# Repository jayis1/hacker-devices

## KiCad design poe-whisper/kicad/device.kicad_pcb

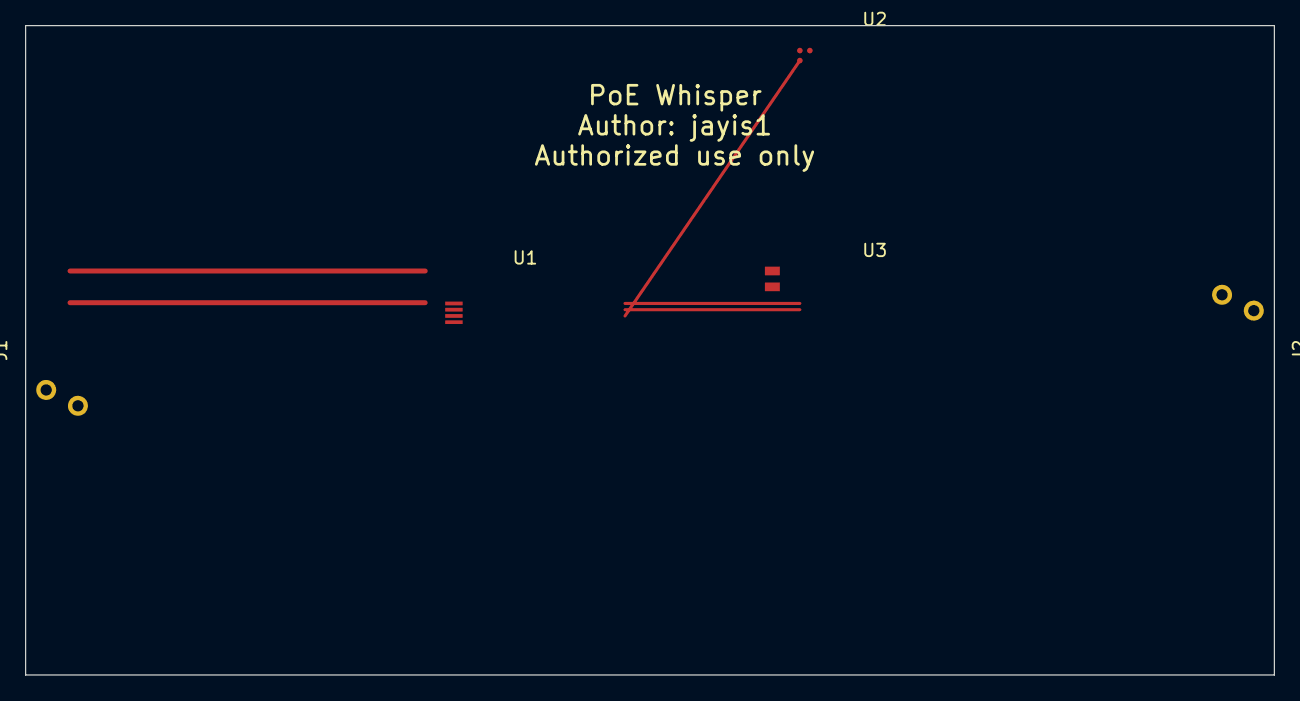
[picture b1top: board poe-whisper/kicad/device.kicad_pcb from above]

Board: 2 copper layers, 100.0 x 52.0 mm, 5 parts (0 on the bottom side), 4 nets.

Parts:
J1: RJ45_PSE_IN; RJ45_Amphenol_RJHSE538X
J2: RJ45_PD_OUT; RJ45_Amphenol_RJHSE538X
U1: STM32H563RIT6; LQFP-64_10x10mm_P0.5mm
U2: MachXO3LF-2100C; caBGA-256_14x14mm_Layout16x16_P0.8mm
U3: ESP32-C3-MINI-1

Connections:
+3V3: U1.4, U3.1
BROWNOUT_GATE: U1.3, U2.B1
POE_RETURN: J1.2, J2.2
POE_VIN: J1.1, J2.1

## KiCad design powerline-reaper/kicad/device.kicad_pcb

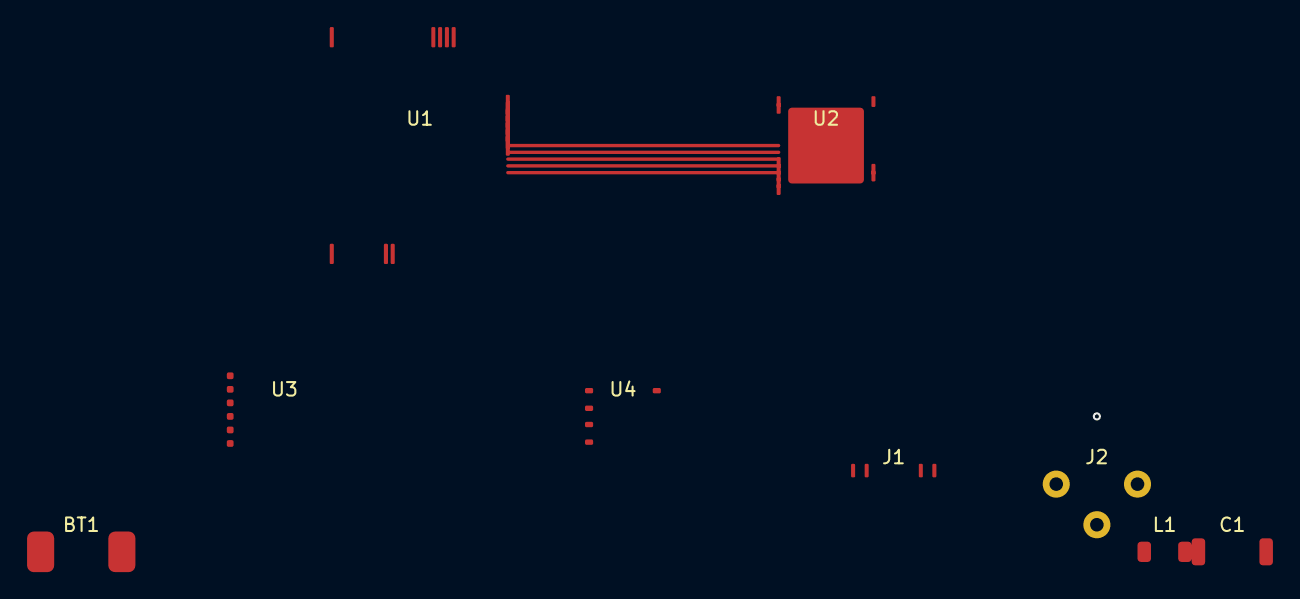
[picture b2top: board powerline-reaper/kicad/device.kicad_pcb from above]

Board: 4 copper layers, 9 parts (0 on the bottom side), 16 nets.

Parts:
BT1: LiPo_1000mAh; BatteryHolder_Keystone_1042
C1: X2Y_100nF_275V; C_2220_5764Metric
J1: USB_C; USB_C_Receptacle
J2: AC_Mains; IEC_C14
L1: CMC_100uH; L_0805_2012Metric
U1: STM32H743VIT6; LQFP-100_14x14mm_P0.5mm
U2: QCA7420; QFN-48-1EP_7x7mm_P0.5mm_EP5.6x5.6mm
U3: nRF52840; nRF52840-module
U4: ADuM1402; SOIC-8_3.9x4.9mm_P1.27mm

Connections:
+3V3: U1.21, U2.1, U3.1
BLE_CTS: U1.81, U3.6
BLE_RTS: U1.80, U3.5
BLE_RX: U1.79, U3.4
BLE_TX: U1.78, U3.3
GND: BT1.-, J1.A1, J2.E, U1.1, U2.2, U2.49, U3.2
LINE_AC: C1.1, J2.L, L1.1, U2.30
NEUTRAL_AC: C1.2, J2.N, L1.2, U2.31
PLC_IRQ: U1.64, U2.14, U4.8
PLC_RST: U1.65, U2.20
SPI_CS: U1.63, U2.13, U4.4
SPI_MISO: U1.62, U2.12, U4.3
SPI_MOSI: U1.61, U2.11, U4.2
SPI_SCK: U1.60, U2.10, U4.1
USB_DM: J1.B11, U1.31
USB_DP: J1.B12, U1.30

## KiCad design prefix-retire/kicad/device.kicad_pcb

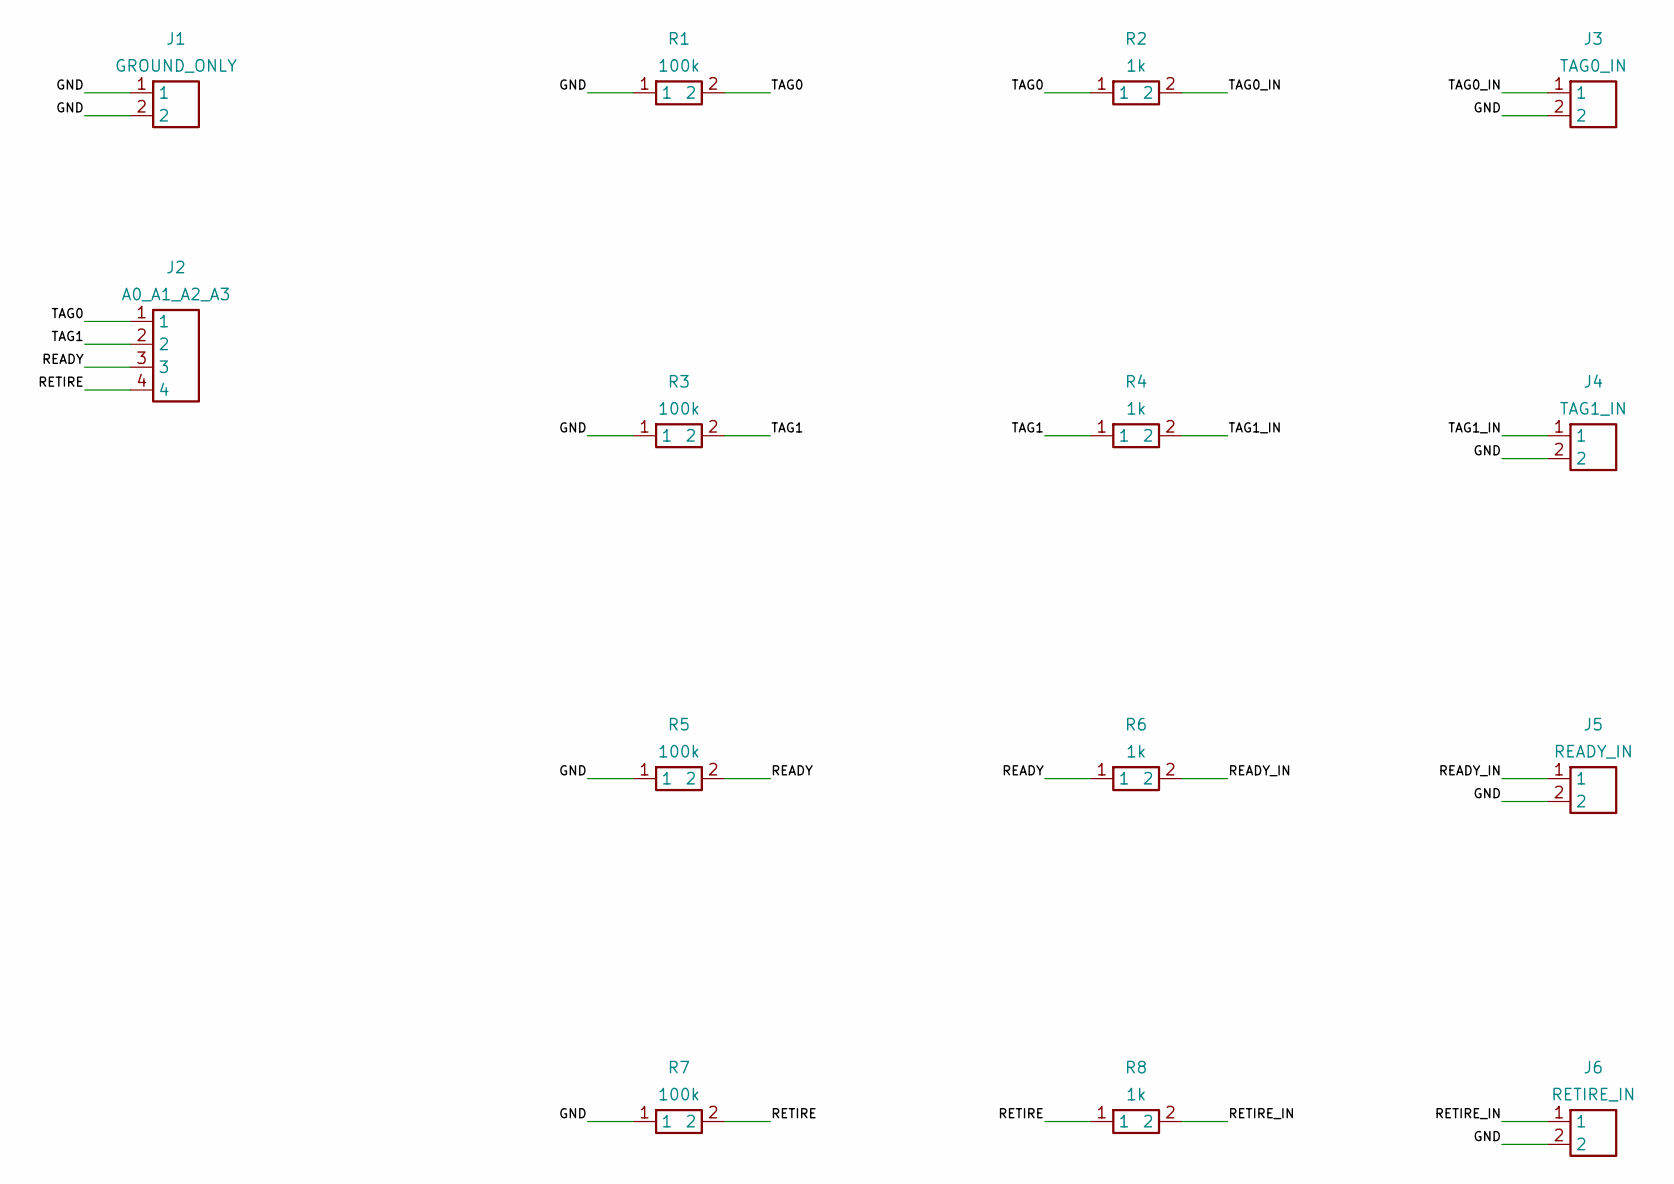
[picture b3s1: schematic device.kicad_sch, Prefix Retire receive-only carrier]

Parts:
J1: GROUND_ONLY; PinHeader_1x02_P2.54mm_Vertical
J2: A0_A1_A2_A3; PinHeader_1x04_P2.54mm_Vertical
J3: TAG0_IN; PinHeader_1x02_P2.54mm_Vertical
J4: TAG1_IN; PinHeader_1x02_P2.54mm_Vertical
J5: READY_IN; PinHeader_1x02_P2.54mm_Vertical
J6: RETIRE_IN; PinHeader_1x02_P2.54mm_Vertical
R1, R3, R5, R7: 100k; R_Axial_DIN0207_L6.3mm_D2.5mm_P7.62mm_Horizontal
R2, R4, R6, R8: 1k; R_Axial_DIN0207_L6.3mm_D2.5mm_P7.62mm_Horizontal

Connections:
GND: J1.1, J1.2, J3.2, J4.2, J5.2, J6.2, R1.1, R3.1, R5.1, R7.1
READY: J2.3, R5.2, R6.1
READY_IN: J5.1, R6.2
RETIRE: J2.4, R7.2, R8.1
RETIRE_IN: J6.1, R8.2
TAG0: J2.1, R1.2, R2.1
TAG0_IN: J3.1, R2.2
TAG1: J2.2, R3.2, R4.1
TAG1_IN: J4.1, R4.2

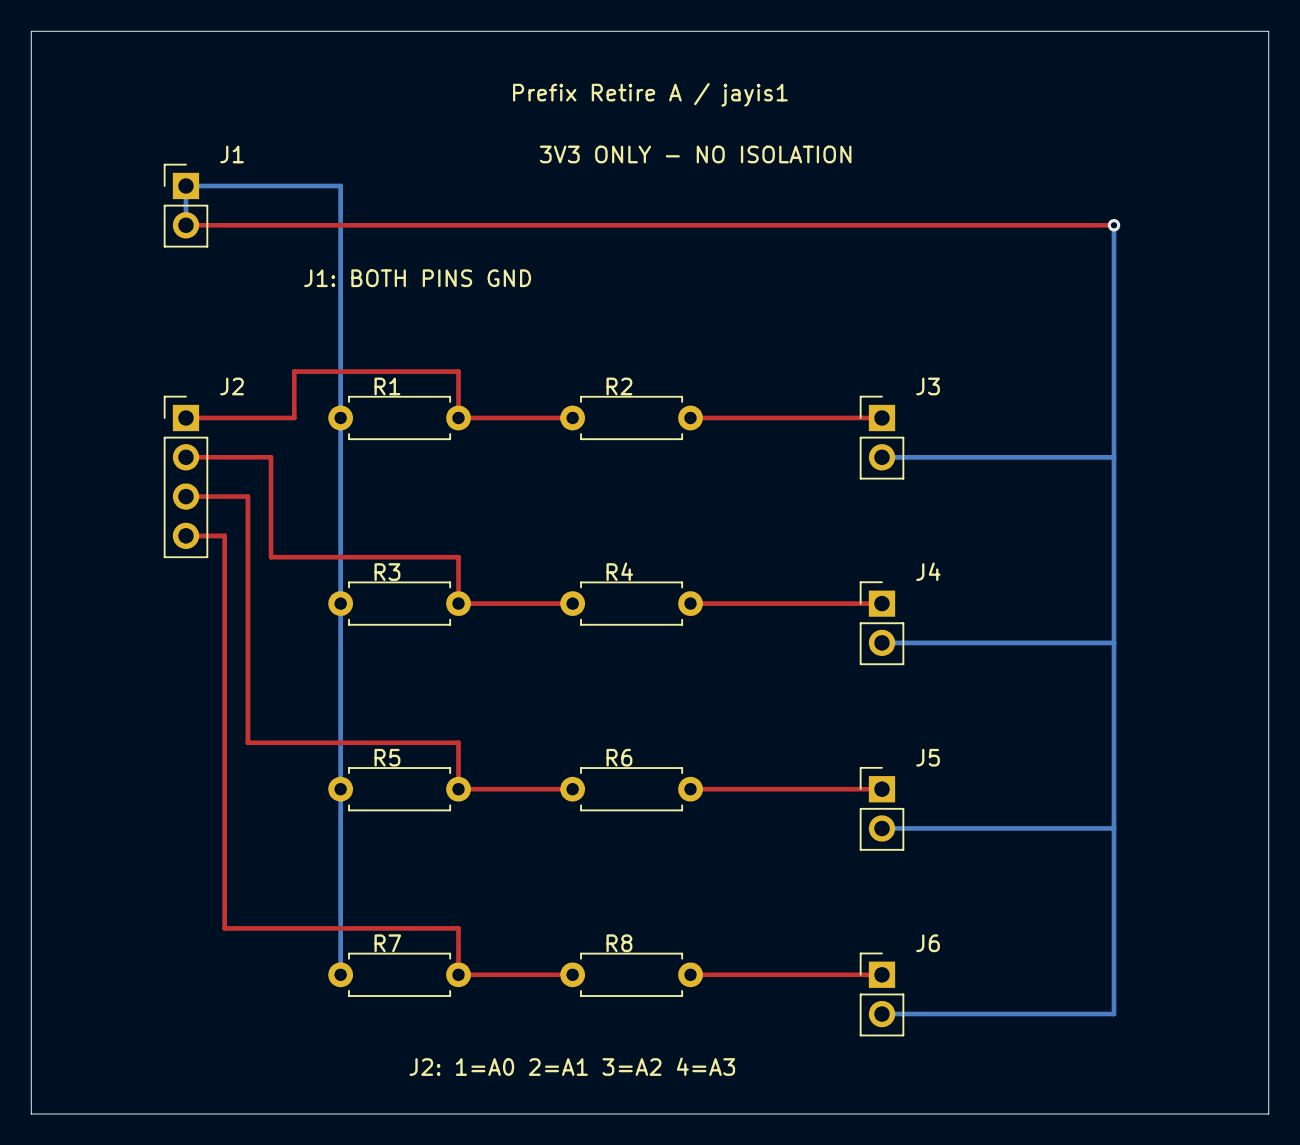
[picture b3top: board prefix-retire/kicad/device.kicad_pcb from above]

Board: 2 copper layers, 80.0 x 70.0 mm, 14 parts (0 on the bottom side), 9 nets.

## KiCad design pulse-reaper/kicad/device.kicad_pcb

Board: 8 copper layers, 11 parts (0 on the bottom side), 12 nets.

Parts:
D1: LED_RG; LED_RGB_1210
J1: USB-C 2.0; USB_C_Receptacle_GCT_USB4105
J2: MicroSD UHS-I; microSD_HC_Hinge
J3: Clamp (off-board); PinHeader_1x06_P2.54mm_Vertical
SW1: MODE; SW_SPST_B3SN_6.0x6.0mm
U1: STM32H743VIT6; LQFP-100_14x14mm_P0.5mm
U2: iCE40UP5K-SG48; QFN-48-1EP_7x7mm_P0.5mm
U3: AD9203ARZ; TSSOP-28_4.4x9.7mm_P0.65mm
U4: LMH5401IRM; VSSOP-8_3.0x3.0mm_P0.65mm
U5: ISO7741DW; SOIC-16W_5.3x10.2mm_P1.27mm
U6: NINA-B306; NINA-B3X

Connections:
BLE_RX: U1.22, U6.4
BLE_TX: U1.21, U6.3
CLAMP_CAP_N: J3.2, U4.6
CLAMP_CAP_P: J3.1, U4.5
FPGA_SPI_CS: U1.15, U2.29
FPGA_SPI_MISO: U1.12, U2.28
FPGA_SPI_MOSI: U1.14, U2.27
FPGA_SPI_SCK: U1.11, U2.26
GND: D1.3, J1.A1, SW1.2, U1.103, U2.25, U5.2, U6.2
ISO_GND2: U4.4, U5.10
ISO_VCC2: U4.1, U5.9
VDD_3V3: J2.4, U1.1, U5.1, U6.1

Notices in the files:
powerline-reaper/kicad/device.kicad_pcb:
Powerline-Reaper PCB — Author: jayis1 — License: CERN-OHL-S v2
prism-tap/kicad/device.kicad_sch:
License: GPL-2.0 / CERN-OHL-S v2
pulse-reaper/kicad/device.kicad_sch:
Author: jayis1 — CERN-OHL-S v2 / GPL-2.0
